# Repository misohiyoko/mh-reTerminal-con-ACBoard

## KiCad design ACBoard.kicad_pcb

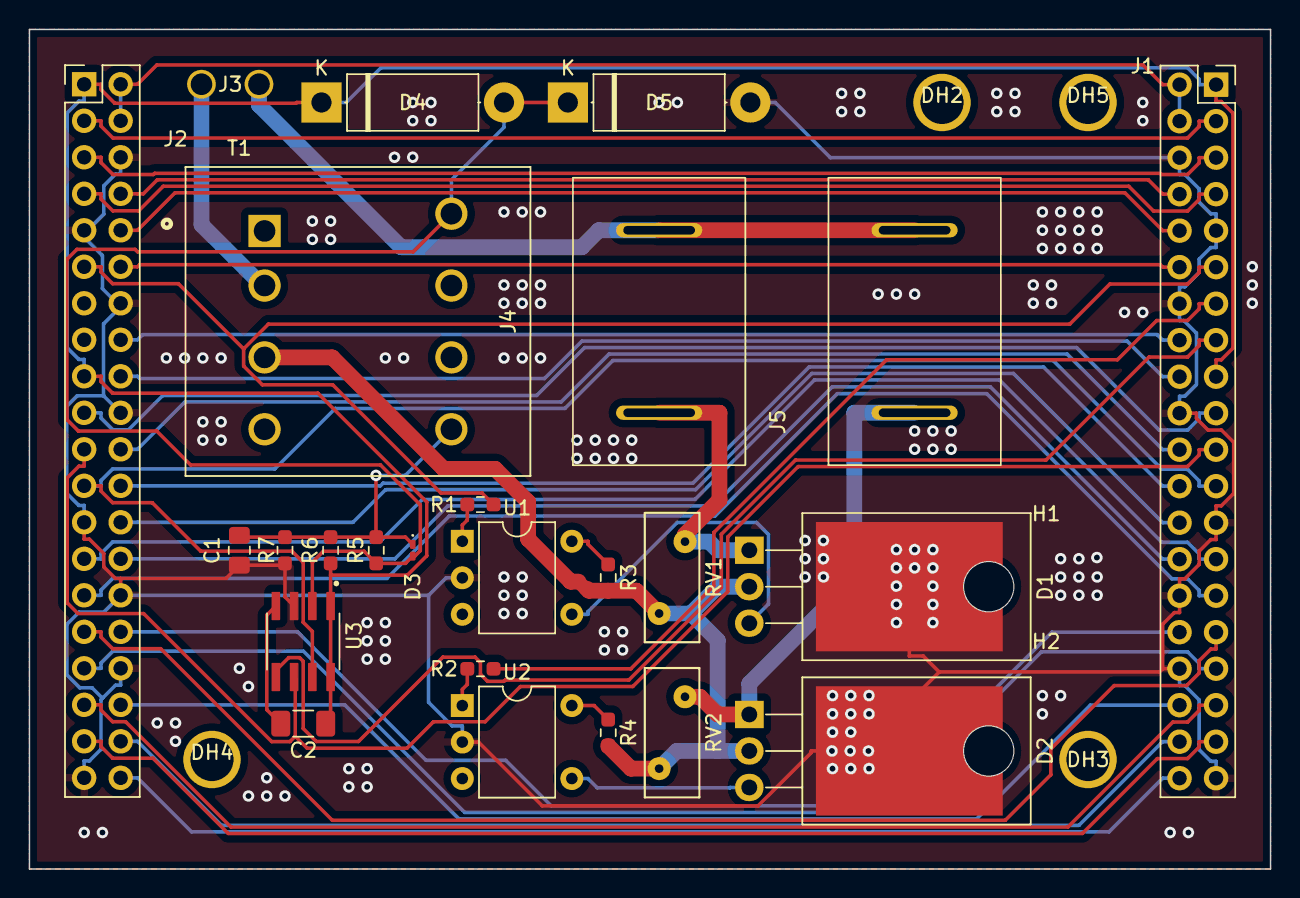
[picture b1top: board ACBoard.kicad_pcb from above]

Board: 2 copper layers, 86.4 x 58.4 mm, 31 parts (0 on the bottom side), 45 nets.

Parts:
C1: 10u; C_0805_2012Metric_Pad1.18x1.45mm_HandSolder
C2: 0.1u; C_1206_3216Metric_Pad1.33x1.80mm_HandSolder
D1, D2: Q_TRIAC_A1A2G; TO-220-3_Horizontal_TabDown
D3: VS3V3BC1EST15R; D_0201_0603Metric_Pad0.64x0.40mm_HandSolder
D4, D5: D; D_5W_P12.70mm_Horizontal
DH2, DH3, DH4, DH5: Drill
H1, H2: heatsink
J1: Conn_02x20_Odd_Even; PinSocket_2x20_P2.54mm_Vertical
J2: Conn_02x20_Odd_Even; PinHeader_2x20_P2.54mm_Vertical
J3: Conn_01x02_Male; ACinlet
J4, J5: Conn_01x02_Female; AcOutlet
R1, R2, R3, R4: 100; R_0603_1608Metric_Pad0.98x0.95mm_HandSolder
R5: 67; R_0603_1608Metric_Pad0.98x0.95mm_HandSolder
R6, R7: 1k; R_0603_1608Metric_Pad0.98x0.95mm_HandSolder
RV1, RV2: Varistor; RV_Disc_D9mm_W3.8mm_P5mm
T1: CSE185L; XFMR_CSE185L
U1, U2: TLP561; DIP-5-6_W7.62mm
U3: ADS7822U; SOIC127P599X175-8N

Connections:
+3V3: C2.1, D4.1 (K), J1.1, J1.17, J2.1, J2.17, R6.1, U3.1 (VREF), U3.8 (+VCC)
+5V: J1.2, J1.4, J2.2, J2.4
/CE0: J1.24, J2.24
/CE1: J1.26, J2.26
/DIN: J1.38, J2.38
/DOUT: J1.40, J2.40
/EEPROM_SCL: J1.28, J2.28
/EEPROM_SDA: J1.27, J2.27
/FS: J1.35, J2.35
/GPIO2: J1.3, J2.3
/GPIO3: J1.5, J2.5
/GPIO4: J1.7, J2.7
/GPIO5: J1.29, J2.29
/GPIO9: J1.21, J2.21, U3.6 (DOUT)
/GPIO10: J1.19, J2.19
/GPIO11: J1.23, J2.23, U3.7 (DCLK)
/GPIO12: J1.32, J2.32
/GPIO14: J1.8, J2.8
/GPIO15: J1.10, J2.10
/GPIO16: J1.36, J2.36
/GPIO17: J1.11, J2.11, R1.1
/GPIO18: J1.12, J2.12
/GPIO22: J1.15, U3.5 (~CS/SHDN)
/GPIO23: J1.16, J2.16
/GPIO24: J1.18, J2.18
/GPIO25: J1.22, J2.22
/GPIO26: J1.37, J2.37
/GPIO27: J1.13, R2.1
/USB_DM: J1.31, J2.31
/USB_DP: J1.33, J2.33
GND: C1.2, D5.2 (A), H1.1, H2.1, J1.6, J1.9, J1.14, J1.20, J1.25, J1.30, J1.34, J1.39, J2.6, J2.9, J2.14, J2.20, J2.25, J2.30, J2.34, J2.39, R7.2, U1.2 (Cathode), U2.2 (Cathode), U3.3 (IN-)
GNDA: J3.2, J4.2, J5.2
unnamed: C1.1, D3.1 (A1), R5.2, R6.2, R7.1, T1.5
unnamed: C2.2, U3.4 (GND)
unnamed: D1.1 (A1), J4.1, RV1.2
unnamed: D1.3 (G), U1.4 (TriacIn)
unnamed: D2.1 (A1), J5.1, RV2.2
unnamed: D2.3 (G), U2.4 (TriacIn)
unnamed: D3.2 (A2), D4.2 (A), D5.1 (K), R5.1, T1.8, U3.2 (IN+)
unnamed: R1.2, U1.1 (Anode)
unnamed: R2.2, U2.1 (Anode)
unnamed: R3.1, U1.6 (TriacIn)
unnamed: R4.1, U2.6 (TriacIn)
unnamed: J3.1, T1.2
VAC: D1.2 (A2), D2.2 (A2), R3.2, R4.2, RV1.1, RV2.1, T1.3

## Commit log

2022-02-22 data10
2022-02-23 data
2022-02-23 data19
2022-02-24 dara2
2022-02-24 AnoTation
2022-02-24 Anotaiton
2022-02-27 data5
2022-03-07 data2
2022-03-07 data3543
2023-11-03 名称未設定ファイル.drawio を追加しました。
